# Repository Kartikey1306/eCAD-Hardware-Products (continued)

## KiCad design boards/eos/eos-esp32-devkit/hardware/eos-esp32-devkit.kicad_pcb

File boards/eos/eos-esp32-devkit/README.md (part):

# EoS ESP32 DevKit

A breadboard development board for the Espressif ESP32-WROOM-32E module, 27.94 × 48.76 mm, two layers.
Designed by Kartikeydheer Srivastava. All rights reserved: not open source, and not under this repository's MIT licence.
Anyone may view it, clone this repository and run its tests; anything more needs
Kartikeydheer Srivastava's written permission (kartikeydheer@gmail.com). EmbeddedOS (EoS) Research Foundation has a limited, revocable
permission. See [LICENSE.txt](LICENSE.txt) and [the licence summary](../README.md#licence).

A board for the same job as Espressif's ESP32-DevKitC V4; an original design, not a copy: no file of the vendor's was used.
The only things taken from Espressif's DevKitC V4 documents are facts it publishes for users: the header
pinout (the user guide's J2 and J3 tables) and the header grid and board width (its dimension drawing).
Its schematic, layout and board files were not opened.

| | |
|---|---|
|  |  |

USB-C in, a CP2102N USB-UART bridge with esptool's automatic reset into the bootloader, a 1 A
3.3 V regulator, EN and BOOT buttons, a power LED and a user LED, and every usable GPIO of the
module on two 1×19 headers.

## What is on it

| Block | What it is, and where each value comes from |
|---|---|
| Module | ESP32-WROOM-32E-N4 (4 MB flash, no PSRAM, so IO16 is free). 22 µF + 100 nF on 3V3 and the EN delay R = 10 kΩ, C = 1 µF: Espressif ESP32-WROOM-32E datasheet v2.1, section 9. The 100 nF and the 1 µF sit in the gap beside the module's 3V3 and EN pins. The module already has a 499 Ω resistor on U0TXD (datasheet Figure 7), as Espressif's hardware design guidelines ask, so none is added. |
| Antenna | The module's whole 6.19 mm antenna area (datasheet Figure 13) overhangs the top edge, 0.31 mm clear of it, so the antenna keep-out lies off the board. This is what the datasheet's section 11.2 refers to: Espressif's hardware design guidelines, "Positioning a Module on a Base Board", put the PCB antenna outside the base board. |
| 3.3 V supply | AP7361C-33 LDO, 1.0 A (Diodes Inc. DS37274 Rev. 5-2). The module needs at least 0.5 A at 3.0–3.6 V (datasheet Table 14) and draws 379 mA at its Wi-Fi TX peak, 239 mA on average (Table 16). Dropout is 140 mV at most at 300 mA. 4.7 µF on input and output, as the regulator's typical application shows. At a 253 mA average load from 4.1–4.8 V (USB's 4.75–5.25 V less the fuse and Schottky drops) it dissipates 0.20–0.39 W, 22–43 °C above ambient at the datasheet's 110 °C/W. |
| USB-C | 5 V sink: 5.1 kΩ Rd on CC1 and CC2 (TI SLVSFJ9, section 10.3.14.2), USB 2.0 data only. SP0503BAHTG ESD protection on D+, D− and VBUS: three diodes to ground, as the CP2102N data sheet shows (Figure 2.5). A USBLC6-style part, whose data-line diodes run to its VBUS pin, would let the CP2102N's D+ pull-up hold VBUS near 2 V after a host unplugs, when the board runs from its 5V pin. 500 mA polyfuse (Littelfuse 1206L050: 0.50 A hold, 1.00 A trip). Then a Nexperia PMEG6010CEH Schottky (60 V, 1 A; VF ≤ 530 mV at 500 mA) to the 5 V rail, so 5 V fed into the 5V pin cannot reach the USB host. It was chosen for its low reverse leakage. From a 4.75 V port at a 400 mA peak the regulator still gets at least 3.94 V. A 5.1 kΩ bleed resistor from VBUS to ground (R12) takes the Schottky's leakage when the board runs from the 5V pin with no host (see VBUS bleed below). |
| USB-UART | CP2102N-A02-GQFN24 (Silicon Labs data sheet Rev. 1.5). The QFN-24 has all eight UART and modem lines (DTR and RTS are the ones needed) in 4 × 4 mm. The QFN-28 is 5 × 5 mm, and its extra pins (battery-charger detection, GPIO.4–6) have no use here. It runs from the 3.3 V rail with its own regulator unused (Figure 2.3), so it is powered whenever the ESP32 is, and the ESP32's TX line never back-powers it. 4.7 µF + 100 nF on VREGIN/VDD and on VIO; 1 kΩ RSTb pull-up (section 2.1). VBUS sense through the 22.1 kΩ / 47.5 kΩ divider (Figures 2.5, 2.6), which section 2.3 requires: 5 V reads as 3.41 V, above the 2.7 V threshold. |
| Auto-program | The two-transistor circuit the esptool documentation describes ("Boot Mode Selection", "Automatic Bootloader"): RTS drives EN, DTR drives IO0, and asserting both together resets nothing. Two MMBT3904 (onsemi), each with its base through 10 kΩ from one line and its emitter on the other. The 10 kΩ gives at least 0.115 mA of base current (CP2102N Table 3.7 levels, MMBT3904 VBE(sat) ≤ 0.85 V) against a 0.33 mA load, so the transistor saturates. Discharging the EN capacitor it passes at most 78 mA into the CP2102N pin, under its 100 mA limit (Table 3.10). The 1 µF on EN is the "1 µF–10 µF" esptool asks for. |
| Buttons | EN (reset) and BOOT (IO0 to ground). IO0 has a 10 kΩ pull-up and no capacitor: Espressif's guidelines ("Strapping Pins") recommend a pull-up on GPIO0 and warn against large capacitors on it. |
| LEDs | Power (red, Kingbright APTD1608LSURCK, VF 1.75 V at 2 mA) through 750 Ω from 3.3 V. User LED (green, APTD1608LCGCK, VF 1.9 V at 2 mA) through 680 Ω on IO4, about 2 mA each. IO4 is not a strapping, JTAG, flash or UART0 pin, and its ADC2 channel cannot be used while Wi-Fi is on. It is pulled down at reset, so the LED starts off. |
| Headers | Two 1×19 rows, 2.54 mm pitch, 25.40 mm apart, on the grid of Espressif's ESP32-DevKitC V4 dimension drawing, in the order of its user guide's J2 and J3 tables. Pin labels are on the back. |

### VBUS bleed

When the board is fed from the 5V pin with no host plugged in, the Schottky is reverse-biased
by about 5 V and leaks into VBUS. Without R12, the CP2102N's 69.6 kΩ VBUS divider would be the
only load on that current, so VBUS could rise until the CP2102N saw a bus that is not there.

The CP2102N is guaranteed to read its VBUS pin as low at or below VIL = 0.6 V. It detects a
bus above VIH = VIO − 0.6 V = 2.7 V (data sheet Rev. 1.5, Table 3.7 and section 2.3). The
divider puts 47.5/69.6 of VBUS on the pin, so VBUS may rise to 0.88 V. R12 in parallel with the
divider is 4.75 kΩ, so up to 185 µA of leakage is harmless.

The PMEG6010CEH leaks 0.8 µA typically at 5 V and 25 °C (Nexperia data sheet v.4, Table 7). Its
maximum, 50 µA at 25 °C, is given at 60 V, and Fig. 2 shows the current falling with the
voltage, so at 5 V it is lower still. That is under a third of the bound. Fig. 2's typical
curves give about 65 µA at 5 V and 85 °C and about 600 µA at 125 °C, so a typical part reaches
185 µA only at roughly 100 °C. The data sheet gives no maximum above 25 °C. Scaling Fig. 2 by
the 25 °C maximum-to-typical ratio (50/11) suggests the bound holds to about 75 °C; that is an
estimate, not a data sheet figure.

With a host attached, R12 draws 1.0 mA (5 mW). It is the same 5.1 kΩ part as the CC resistors.
The PMEG6010CEH's forward drop is higher than a low-voltage Schottky's (460 mV typical, 530 mV
maximum at 500 mA), which the supply budget above allows for.

### Headers

Pin 1 is at the antenna end. Pin numbers and names follow the ESP32-DevKitC V4 user guide.

| Pin | J2 (left) | J3 (right) |
|---|---|---|
| 1 | 3V3 | GND |
| 2 | EN | IO23 |
| 3 | IO36 (SENSOR_VP, input only) | IO22 |
| 4 | IO39 (SENSOR_VN, input only) | TX (IO1, U0TXD) |
| 5 | IO34 (input only) | RX (IO3, U0RXD) |
| 6 | IO35 (input only) | IO21 |
| 7 | IO32 | GND |
| 8 | IO33 | IO19 |
| 9 | IO25 | IO18 |
| 10 | IO26 | IO5 (strapping) |
| 11 | IO27 | IO17 |
| 12 | IO14 | IO16 |
| 13 | IO12 (strapping: keep low at reset) | IO4 (user LED) |
| 14 | GND | IO0 (BOOT) |
| 15 | IO13 | IO2 (strapping: low or open to flash) |
| 16 | not connected | IO15 (strapping) |
| 17 | not connected | not connected |
| 18 | not connected | not connected |
| 19 | 5V | not connected |

The six unconnected positions are where the DevKitC V4 tables put D0–D3, CMD and CLK, which
are GPIO6–GPIO11. On the ESP32-WROOM-32E those lines run to the module's own SPI flash and are
not led out: the datasheet lists module pins 17–22 as NC (Table 3, note 2). They stay
unconnected here, so nothing can be wired to the flash bus.

Power: USB-C, the 5V pin and the 3V3 pin can each power the board. Espressif's DevKitC V4 guide
says to use one and only one supply on its board. This board allows one combination more:
USB-C and the 5V pin may be connected together. The Schottky between VBUS and the 5 V rail
stops the 5V-pin supply feeding back into the USB host. The board then runs from the 5V pin
unless that is lower than VBUS less the Schottky's drop. The 3V3 pin is wired straight to the
regulator's output, so use it as an input only when nothing is connected to USB-C or the 5V
pin.

The module overhangs the top edge by about 6.5 mm (its antenna end is 6.50 mm past the edge).
A panel of these boards needs a clear zone at least that deep above the top edge, with no
frame or neighbouring board in it.

The board is 0.50 mm longer than the DevKitC V4's 48.26 mm. The pin rows start 1.75 mm below
the top edge instead of 1.25 mm, because the header courtyards must clear the module
footprint's antenna keep-out courtyard. The grid itself (row spacing, pitch, side margins,
bottom margin) is unchanged, so the board fits the same breadboard rows and carrier sockets.

## Not on this board

- **Other modules.** Espressif sells the DevKitC V4 with several modules (WROOM-32UE, WROVER-E
  and others). This board is for the ESP32-WROOM-32E only, without PSRAM.
- **GPIO6–GPIO11 on the headers.** The WROOM-32E does not lead them out (see above).
- **Female headers.** The DevKitC V4 is also sold with female headers. This design uses male
  pin headers.
- **The DevKitC V4's exact length.** It is 0.50 mm longer, for the reason given above.
- **Mounting holes.** There is no room between the header rows for them. The board is meant
  for a breadboard or a socket.
- **An on-board debug probe.** The DevKitC V4 has none, and neither does this board. The
  module's JTAG pins (IO12 MTDI, IO13 MTCK, IO14 MTMS, IO15 MTDO) are on the headers for an
  external JTAG adapter.

## Build results

The numbers below are from `build-report.json` and `drc.json` in this folder.

| Check | Result |
|---|---|
| Schematic ERC | 0 violations |
| DRC errors | 0 |
| Unconnected items | 0 |
| Schematic ↔ board parity | 0 differences |
| DRC warnings | 8: silkscreen past the board edge: the header rows and the USB-C connector sit at the edge, and the module's outline runs over its antenna overhang |

## Fabrication

2 layers, 1.6 mm thick, ground poured on both sides. Design rules:

- **Tracks:** 0.15 mm, narrowing to the 0.1 mm minimum at fine-pitch pads; 0.4 mm on the
  supplies (VBUS, the fuse-to-Schottky link, 5 V and 3.3 V); 0.2 mm on USB D+/D−.
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
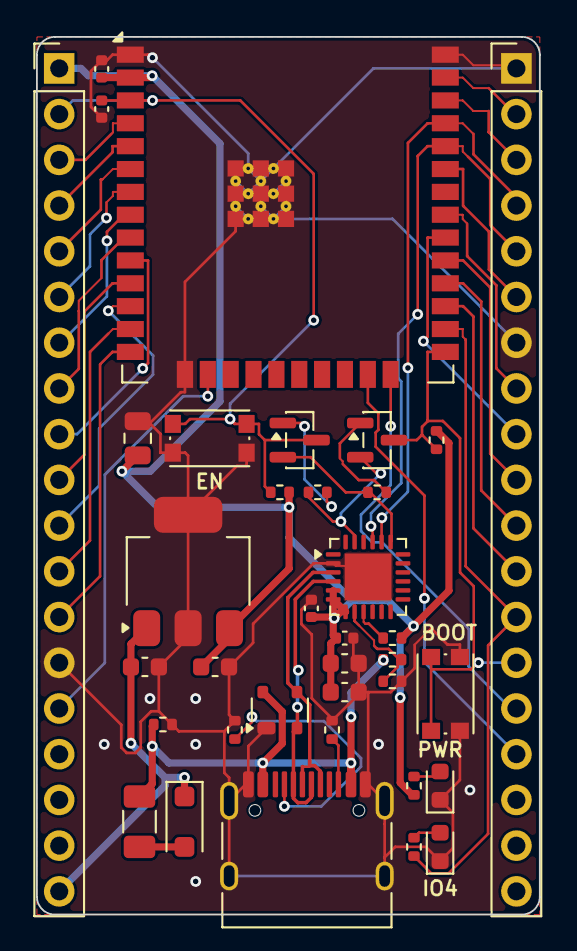
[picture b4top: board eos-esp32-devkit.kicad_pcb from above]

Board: 2 copper layers, 27.9 x 48.8 mm, 36 parts (0 on the bottom side), 44 nets.

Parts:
C1, C2, C6, C8: 4.7u; C_0603_1608Metric
C3, C7, C9: 100n; C_0402_1005Metric
C4: 22u; C_0805_2012Metric
C5: 1u; C_0402_1005Metric
D1: PMEG6010CEH; D_SOD-123F
D2: PWR; LED_0603_1608Metric
D3: IO4; LED_0603_1608Metric
F1: 500mA; Fuse_1206_3216Metric
J1: USB-C; USB_C_Receptacle_HRO_TYPE-C-31-M-12
J2: J2; PinHeader_1x19_P2.54mm_Vertical
J3: J3; PinHeader_1x19_P2.54mm_Vertical
Q1, Q2: MMBT3904; SOT-23
R1, R2, R12: 5.1k; R_0402_1005Metric
R3: 750; R_0402_1005Metric
R4, R5, R10, R11: 10k; R_0402_1005Metric
R6: 680; R_0402_1005Metric
R7: 1k; R_0402_1005Metric
R8: 22.1k; R_0402_1005Metric
R9: 47.5k; R_0402_1005Metric
SW1: EN; SW_Push_1P1T_NO_CK_KMR2
SW2: BOOT; SW_Push_1P1T_NO_CK_KMR2
U1: ESP32-WROOM-32E-N4; ESP32-WROOM-32E
U2: SP0503BAHTG; SOT-143
U3: AP7361C-33; SOT-223-3_TabPin2
U4: CP2102N-A02-GQFN24; QFN-24-1EP_4x4mm_P0.5mm_EP2.6x2.6mm

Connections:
+3V3: C2.1, C3.1, C4.1, C6.1, C7.1, C8.1, C9.1, J2.1, R3.1, R4.2, R5.2, R7.2, U1.2, U3.3, U4.5, U4.6, U4.7
+5V: C1.1, D1.1, J2.19, U3.1
/CC1: J1.A5, R1.1
/CC2: J1.B5, R2.1
/CP_RST: R7.1, U4.9
/DTR: Q2.2, R10.1, U4.23
/EN: C5.2, J2.2, Q1.3, R4.1, SW1.1, U1.3
/IO0: J3.14, Q2.3, R5.1, SW2.1, U1.25
/IO2: J3.15, U1.24
/IO4: J3.13, R6.1, U1.26
/IO5: J3.10, U1.29
/IO12: J2.13, U1.14
/IO13: J2.15, U1.16
/IO14: J2.12, U1.13
/IO15: J3.16, U1.23
/IO16: J3.12, U1.27
/IO17: J3.11, U1.28
/IO18: J3.9, U1.30
/IO19: J3.8, U1.31
/IO21: J3.6, U1.33
/IO22: J3.3, U1.36
/IO23: J3.2, U1.37
/IO25: J2.9, U1.10
/IO26: J2.10, U1.11
/IO27: J2.11, U1.12
/IO32: J2.7, U1.8
/IO33: J2.8, U1.9
/IO34: J2.5, U1.6
/IO35: J2.6, U1.7
/IO36: J2.3, U1.4
/IO39: J2.4, U1.5
/LED_PWR_A: D2.2, R3.2
/LED_USR_A: D3.2, R6.2
/QB1: Q1.1, R10.2
/QB2: Q2.1, R11.2
/RTS: Q1.2, R11.1, U4.19
/U0RXD: J3.5, U1.34, U4.21
/U0TXD: J3.4, U1.35, U4.20
/USB_D+: J1.A6, J1.B6, U2.3, U4.3
/USB_D-: J1.A7, J1.B7, U2.2, U4.4
/VBUS_F: D1.2, F1.2
/VBUS_SENSE: R8.2, R9.1, U4.8
GND: C1.2, C2.2, C3.2, C4.2, C5.1, C6.2, C7.2, C8.2, C9.2, D2.1, D3.1, J1.A1, J1.A12, J1.B1, J1.B12, J1.SH, J2.14, J3.1, J3.7, R1.2, R2.2, R9.2, R12.2, SW1.2, SW2.2, U1.1, U1.15, U1.38, U1.39, U2.1, U3.2, U4.2, U4.25
VBUS: F1.1, J1.A4, J1.A9, J1.B4, J1.B9, R8.1, R12.1, U2.4

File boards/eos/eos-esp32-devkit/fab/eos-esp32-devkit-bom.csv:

"Refs","Value","Footprint","Manufacturer","MPN","Description","Qty","DNP"
"C1,C2,C6,C8","4.7u","Capacitor_SMD:C_0603_1608Metric","","","Capacitor 4.7 uF 10 V X5R 0603 (CP2102N VIO, Silicon Labs CP2102N data sheet Rev. 1.5 section 2.1),Capacitor 4.7 uF 10 V X5R 0603 (CP2102N VREGIN/VDD, Silicon Labs CP2102N data sheet Rev. 1.5 Figure 2.3),Capacitor 4.7 uF 10 V X5R 0603 (LDO input; DS37274 typical application),Capacitor 4.7 uF 10 V X5R 0603 (LDO output; DS37274 typical application)","4",""
"C3,C7,C9","100n","Capacitor_SMD:C_0402_1005Metric","","","Capacitor 100 nF X7R 0402 (CP2102N VIO, Silicon Labs CP2102N data sheet Rev. 1.5 section 2.1),Capacitor 100 nF X7R 0402 (CP2102N VREGIN/VDD, Silicon Labs CP2102N data sheet Rev. 1.5 Figure 2.3),Capacitor 100 nF X7R 0402 (module 3V3, C2 in Espressif ESP32-WROOM-32E datasheet v2.1 section 9)","3",""
"C4","22u","Capacitor_SMD:C_0805_2012Metric","","","Capacitor 22 uF 10 V X5R 0805 (module 3V3, C1 in Espressif ESP32-WROOM-32E datasheet v2.1 section 9)","1",""
"C5","1u","Capacitor_SMD:C_0402_1005Metric","","","Capacitor 1 uF X7R 0402 (EN RC delay, Espressif ESP32-WROOM-32E datasheet v2.1 section 9; esptool needs 1-10 uF on EN for auto-reset)","1",""
"D1","PMEG6010CEH","Diode_SMD:D_SOD-123F","Nexperia","PMEG6010CEH","Schottky 60 V 1 A, VF <= 530 mV at 500 mA, IR 0.8 uA typ at 5 V, <= 50 uA at 25 C (Nexperia PMEG6010CEH v.4): the 5V pin cannot feed the USB host","1",""
"D2","PWR","LED_SMD:LED_0603_1608Metric","Kingbright","APTD1608LSURCK","LED red 0603, power (VF 1.75 V typ at 2 mA, DSAO7433)","1",""
"D3","IO4","LED_SMD:LED_0603_1608Metric","Kingbright","APTD1608LCGCK","LED green 0603, user LED on IO4 (VF 1.9 V typ at 2 mA, DSAO7432)","1",""
"F1","500mA","Fuse:Fuse_1206_3216Metric","Littelfuse","1206L050YR","PTC resettable fuse 0.50 A hold, 1.00 A trip, 6 V, 1206 (Littelfuse 1206L datasheet)","1",""
"J1","USB-C","Connector_USB:USB_C_Receptacle_HRO_TYPE-C-31-M-12","Korean Hroparts","TYPE-C-31-M-12","USB-C 2.0 receptacle, 16 pins (USB 2.0 only)","1",""
"J2","J2","Connector_PinHeader_2.54mm:PinHeader_1x19_P2.54mm_Vertical","","","Pin header 1x19 2.54 mm, left row (DevKitC V4 J2 pinout; 16-18 unconnected)","1",""
"J3","J3","Connector_PinHeader_2.54mm:PinHeader_1x19_P2.54mm_Vertical","","","Pin header 1x19 2.54 mm, right row (DevKitC V4 J3 pinout; 17-19 unconnected)","1",""
"Q1,Q2","MMBT3904","Package_TO_SOT_SMD:SOT-23","onsemi","MMBT3904LT1G","NPN, auto-boot: DTR low (RTS high) pulls IO0 low,NPN, auto-reset: RTS low (DTR high) pulls EN low","2",""
"R1,R2,R12","5.1k","Resistor_SMD:R_0402_1005Metric","","","Resistor 5.1 kohm 1% 0402 (USB-C sink Rd on CC1, 5.1 kohm per TI SLVSFJ9 section 10.3.14.2),Resistor 5.1 kohm 1% 0402 (USB-C sink Rd on CC2, 5.1 kohm per TI SLVSFJ9 section 10.3.14.2),Resistor 5.1 kohm 1% 0402 (VBUS bleed: with the divider, 4.75 kohm, so up to 185 uA of D1 leakage keeps the CP2102N VBUS pin under VIL 0.6 V, Silicon Labs CP2102N data sheet Rev. 1.5 Table 3.7; PMEG6010CEH leaks <= 50 uA at 25 C; 1.0 mA from a host)","3",""
"R3","750","Resistor_SMD:R_0402_1005Metric","","","Resistor 750 ohm 1% 0402 (power LED, 2.1 mA at VF 1.75 V; Kingbright DSAO7433)","1",""
"R4,R5,R10,R11","10k","Resistor_SMD:R_0402_1005Metric","","","Resistor 10 kohm 1% 0402 (EN RC delay, Espressif ESP32-WROOM-32E datasheet v2.1 section 9),Resistor 10 kohm 1% 0402 (IO0 pull-up, Espressif guidelines 'Strapping Pins'; internal pull-up 45 kohm),Resistor 10 kohm 1% 0402 (Q1 base; >= 0.115 mA, MMBT3904LT1/D and CP2102N Table 3.7),Resistor 10 kohm 1% 0402 (Q2 base; >= 0.115 mA, MMBT3904LT1/D and CP2102N Table 3.7)","4",""
"R6","680","Resistor_SMD:R_0402_1005Metric","","","Resistor 680 ohm 1% 0402 (user LED, 2.1 mA at VF 1.9 V; Kingbright DSAO7432)","1",""
"R7","1k","Resistor_SMD:R_0402_1005Metric","","","Resistor 1 kohm 1% 0402 (CP2102N RSTb pull-up, Silicon Labs CP2102N data sheet Rev. 1.5 section 2.1)","1",""
"R8","22.1k","Resistor_SMD:R_0402_1005Metric","","","Resistor 22.1 kohm 1% 0402 (CP2102N VBUS divider, Silicon Labs CP2102N data sheet Rev. 1.5 Figure 2.5)","1",""
"R9","47.5k","Resistor_SMD:R_0402_1005Metric","","","Resistor 47.5 kohm 1% 0402 (CP2102N VBUS divider, Silicon Labs CP2102N data sheet Rev. 1.5 Figure 2.5)","1",""
"SW1","EN","Button_Switch_SMD:SW_Push_1P1T_NO_CK_KMR2","C&K","KMR221G LFS","Tactile switch, EN (reset)","1",""
"SW2","BOOT","Button_Switch_SMD:SW_Push_1P1T_NO_CK_KMR2","C&K","KMR221G LFS","Tactile switch, BOOT (IO0 low: download mode)","1",""
"U1","ESP32-WROOM-32E-N4","RF_Module:ESP32-WROOM-32E","Espressif","ESP32-WROOM-32E-N4","ESP32 module, 4 MB flash, no PSRAM, PCB antenna (pins 17-22 and 32 NC, datasheet v2.1 Table 3)","1",""
"U2","USBLC6-2SC6","Package_TO_SOT_SMD:SOT-23-6","STMicroelectronics","USBLC6-2SC6","USB ESD protection, D+/D- and VBUS (ST DS4260 Rev. 7)","1",""
"U3","AP7361C-33","Package_TO_SOT_SMD:SOT-223-3_TabPin2","Diodes Incorporated","AP7361C-33E-13","LDO 3.3 V 1.0 A, SOT-223 (Diodes DS37274 Rev. 5-2); module needs >= 0.5 A","1",""
"U4","CP2102N-A02-GQFN24","Package_DFN_QFN:QFN-24-1EP_4x4mm_P0.5mm_EP2.6x2.6mm","Silicon Labs","CP2102N-A02-GQFN24R","USB-UART bridge, QFN-24, own regulator unused (Silicon Labs CP2102N data sheet Rev. 1.5 Figure 2.3)","1",""

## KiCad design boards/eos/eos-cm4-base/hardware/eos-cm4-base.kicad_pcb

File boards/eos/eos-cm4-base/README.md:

# EoS CM4 Base

A carrier board for the Raspberry Pi Compute Module 4, 90 × 80 mm, four layers. Designed by
Kartikeydheer Srivastava. All rights reserved: not open source, and not under this repository's MIT licence.
Anyone may view it, clone this repository and run its tests; anything more needs
Kartikeydheer Srivastava's written permission (kartikeydheer@gmail.com). EmbeddedOS (EoS) Research Foundation has a limited, revocable
permission. See [LICENSE.txt](LICENSE.txt) and [the licence summary](../README.md#licence).

A board for the same job as Raspberry Pi's CM4 IO Board; an original design, not a copy: no file
of the CM4 IO Board was used. It is EoS CM5 Base's layout, changed where the CM4 differs. The
connector and hole positions are facts taken from the CM5 footprint that Raspberry Pi publishes
for carrier designs (the CM5 IO Board datasheet says it may be used in your own designs). They
are cross-checked against the dimensions in the CM4 datasheet's Figure 4.

| | |
|---|---|
|  |  |

## The module fits, to the nanometre

The CM4 plugs in through two 100-pin Hirose DF40C-100DS-0.4V connectors, giving 1.5 mm
stacking (CM4 datasheet, section 3.1).

**Where the connectors and holes go.** Figure 4 of the CM4 datasheet and Figure 4 of the CM5
datasheet show the same module:
- the same 55 × 40 mm outline;
- M2.5 holes inset 3.5 mm;
- connectors 3 mm from the long edges;
- the same wireless cut-out.

The CM5 datasheet (section 1.2) also says CM5 fits existing CM4 carrier boards. So the connector
pads and holes sit where `tools/eos_boards/reference/cm5_carrier.json` puts them. That file holds
facts from the CM5 footprint that Raspberry Pi publishes for carriers. A test also places the
holes and connector centres from Figure 4's own dimensions and checks they land in the same
spots.

**Which net each pin carries** comes from the CM4 datasheet's pinout (section 4). It is recorded
in `tools/eos_boards/reference/cm4_pins.json` by `extract_cm4.py`, with the datasheet's SHA-256.

`tests/unit/test_eos_boards.py` checks, at KiCad's 1 nm resolution:
- all 200 pads and the four holes;
- every ground, 5 V, 3.3 V and GPIO pin's net;
- that HDMI, camera, display, PCIe, 1.8 V and reserved pins stay unconnected.

## What is on it

| Block | How |
|---|---|
| Power in | **USB-C, 5 V / 3 A.** VBUS feeds the module's six +5V pins (4.75–5.25 V). The CM4 draws about 1.4 A when running (datasheet section 5.3), plus the USB-A port (0.5 A), the 3.3 V loads and the fan, so use a 5 V / 3 A supply; a computer's USB port may not power the board. The CM4 does not negotiate USB-C power, so CC1 and CC2 each have 5.1 kΩ to ground (a USB-C sink). They also go to AnalogIP1 and AnalogIP0, which the datasheet says are "typically connected to CC pin of Type C power connector". The header's 5 V pins share this rail with no diode, so a HAT must not feed 5 V while the board is off. |
| USB 2.0 | **One port, two connectors.** The CM4 has one USB 2.0 port. A jumper (J9 5–6) chooses where it goes: open, a TI TS3USB30E switch routes it to the USB-C connector (device: rpiboot flashing, gadget mode); fitted, to the USB-A connector (host). TI's truth table: S low, D = D1; S high, D = D2. The same line is USB_OTG_ID: "Internally pulled up. When grounded the CM4 becomes a USB host but the correct OS driver also needs to be used" (pin 101). **The OS sets the role.** USB is off until `otg_mode=1` in `config.txt` enables it (section 2.4), and the ID pin is read only in OTG mode, so set the jumper to match. Fit it for host use. Leave it open for rpiboot, which always needs it open, and for gadget use (for example `dtoverlay=dwc2,dr_mode=peripheral`). **The USB-A port** sits on the top edge beside the module's USB pins, so the host path is short; the generator does not match lengths. Its 5 V comes through a TPS2051C (0.5 A, enable active high), whose enable a 2N7002 drives. It is on only in host mode and only while the CM4's 3.3 V is up: tied straight to USB_OTG_ID, an active-low switch would turn on whenever that rail is down. There are 0.1 µF and 10 µF at the input and 0.1 µF ceramic and 150 µF at the output, after TI's application circuit (USB asks 120 µF per port). Both connectors have USBLC6-2SC6 ESD protection. |
| Gigabit Ethernet | As EoS CM5 Base: a TRXCOM TRJG0926HENL MagJack, pairs 0–3 to TRD0–3, centre tap through 100 nF, activity and speed LEDs (Ethernet_nLED3, nLED2) through 470 Ω, and two flow-through TPD4EUSB30 for ESD. The CM4 uses the same pins. |
| microSD (CM4 Lite) | As EoS CM5 Base: direct to SD_CLK, SD_CMD and SD_DAT0–3. The card's 3.3 V comes through an RT9742GGJ5 switch enabled by SD_PWR_ON. |
| 40-pin GPIO | The standard Raspberry Pi header. GPIO_VREF is tied to CM4_3.3V, as the datasheet requires for 3.3 V GPIO. |
| Controls and LEDs | **Reset:** RUN_PG can be "driven low (via a 220Ω resistor) to reset the CM4 CPU", so a reset button goes through 220 Ω. **Power LED:** PI_LED_nPWR "needs to be buffered", so a BSS84 P-MOSFET drives it. **Activity LED:** Pi_nLED_Activity sinks its LED directly (20 mA max). **Jumpers:** nRPIBOOT (USB boot), EEPROM write protect, USB host mode. **Fan:** a plain 5 V fan connector. |
| Antenna | **No copper on any layer under the module's PCB antenna.** The CM4 datasheet (section 3.1) says there must be no metal there, ground planes included, and a ground-plane cut-out of at least 6.5 × 11 mm, ideally 8 × 15 mm. The board keeps the larger area clear on every layer, where Figure 4 puts the antenna. A test checks it. |

## Not on this board

HDMI, PCIe, and the camera and display (MIPI CSI and DSI) interfaces are left off on purpose.
Each needs impedance-controlled, length-matched differential pairs. This generator routes nets
one at a time and cannot match or verify such pairs.

The CM4 has no RTC battery input and no fan-controller pins, so this board has no coin cell and
no fan speed control. Raspberry Pi's CM4 IO Board adds those with chips on I2C; this board does
not.

## Build results

The numbers below are from `build-report.json` and `drc.json` in this folder.

| Check | Result |
|---|---|
| Schematic ERC | 0 violations |
| DRC errors | 0 |
| Unconnected items | 0 |
| Schematic ↔ board parity | 0 differences |
| DRC warnings | 4: silkscreen of the USB-C connector (J3) and the RJ45 MagJack (J5) past the board edge, where edge connectors belong |

## Fabrication

4 layers (signal / GND plane / 5 V plane / signal), 1.6 mm thick.

- **Vias:** 0.45 mm with a 0.2 mm drill, as on EoS CM5 Base.
- **Tracks:** 0.15 mm by default and 0.2 mm on the USB and Ethernet lines, narrowing to the 0.09 mm
  four-layer minimum where the router enters a fine-pitch pad; 0.5 mm on 5 V where it is routed
  rather than on the plane.
- **Under the module:** nothing on the top side, because 1.5 mm stacking leaves no room. There is
  no copper at all under the antenna.

Some lines are routed first, in a set order, before the autorouter:
- the Ethernet pairs;
- the USB pair from the module to the switch;
- the host pair through its ESD part to the USB-A port;
- three microSD lines (DAT1, DAT0, CLK).

The power switch and the 150 µF capacitor sit more than 10 mm from the module's antenna.

## What has not been done

- **No board has been made or tested.**
- **No signal-integrity simulation.** The CM4 datasheet asks for 90 Ω differential pairs with P
  and N matched to 0.15 mm, and TI asks for equal-length USB lines. This generator routes each
  line on its own and matches no lengths, so the pairs are short but not matched, and their
  impedance has not been calculated or simulated.
- **The switch's effect on the USB eye** has not been measured. TI publishes a 480 Mb/s eye
  diagram through the TS3USB30E.

## Rebuild

```
python3 tools/eos_boards/build.py eos_cm4_base
```

The design file is [tools/eos_boards/boards/eos_cm4_base.py](../../../tools/eos_boards/boards/eos_cm4_base.py).

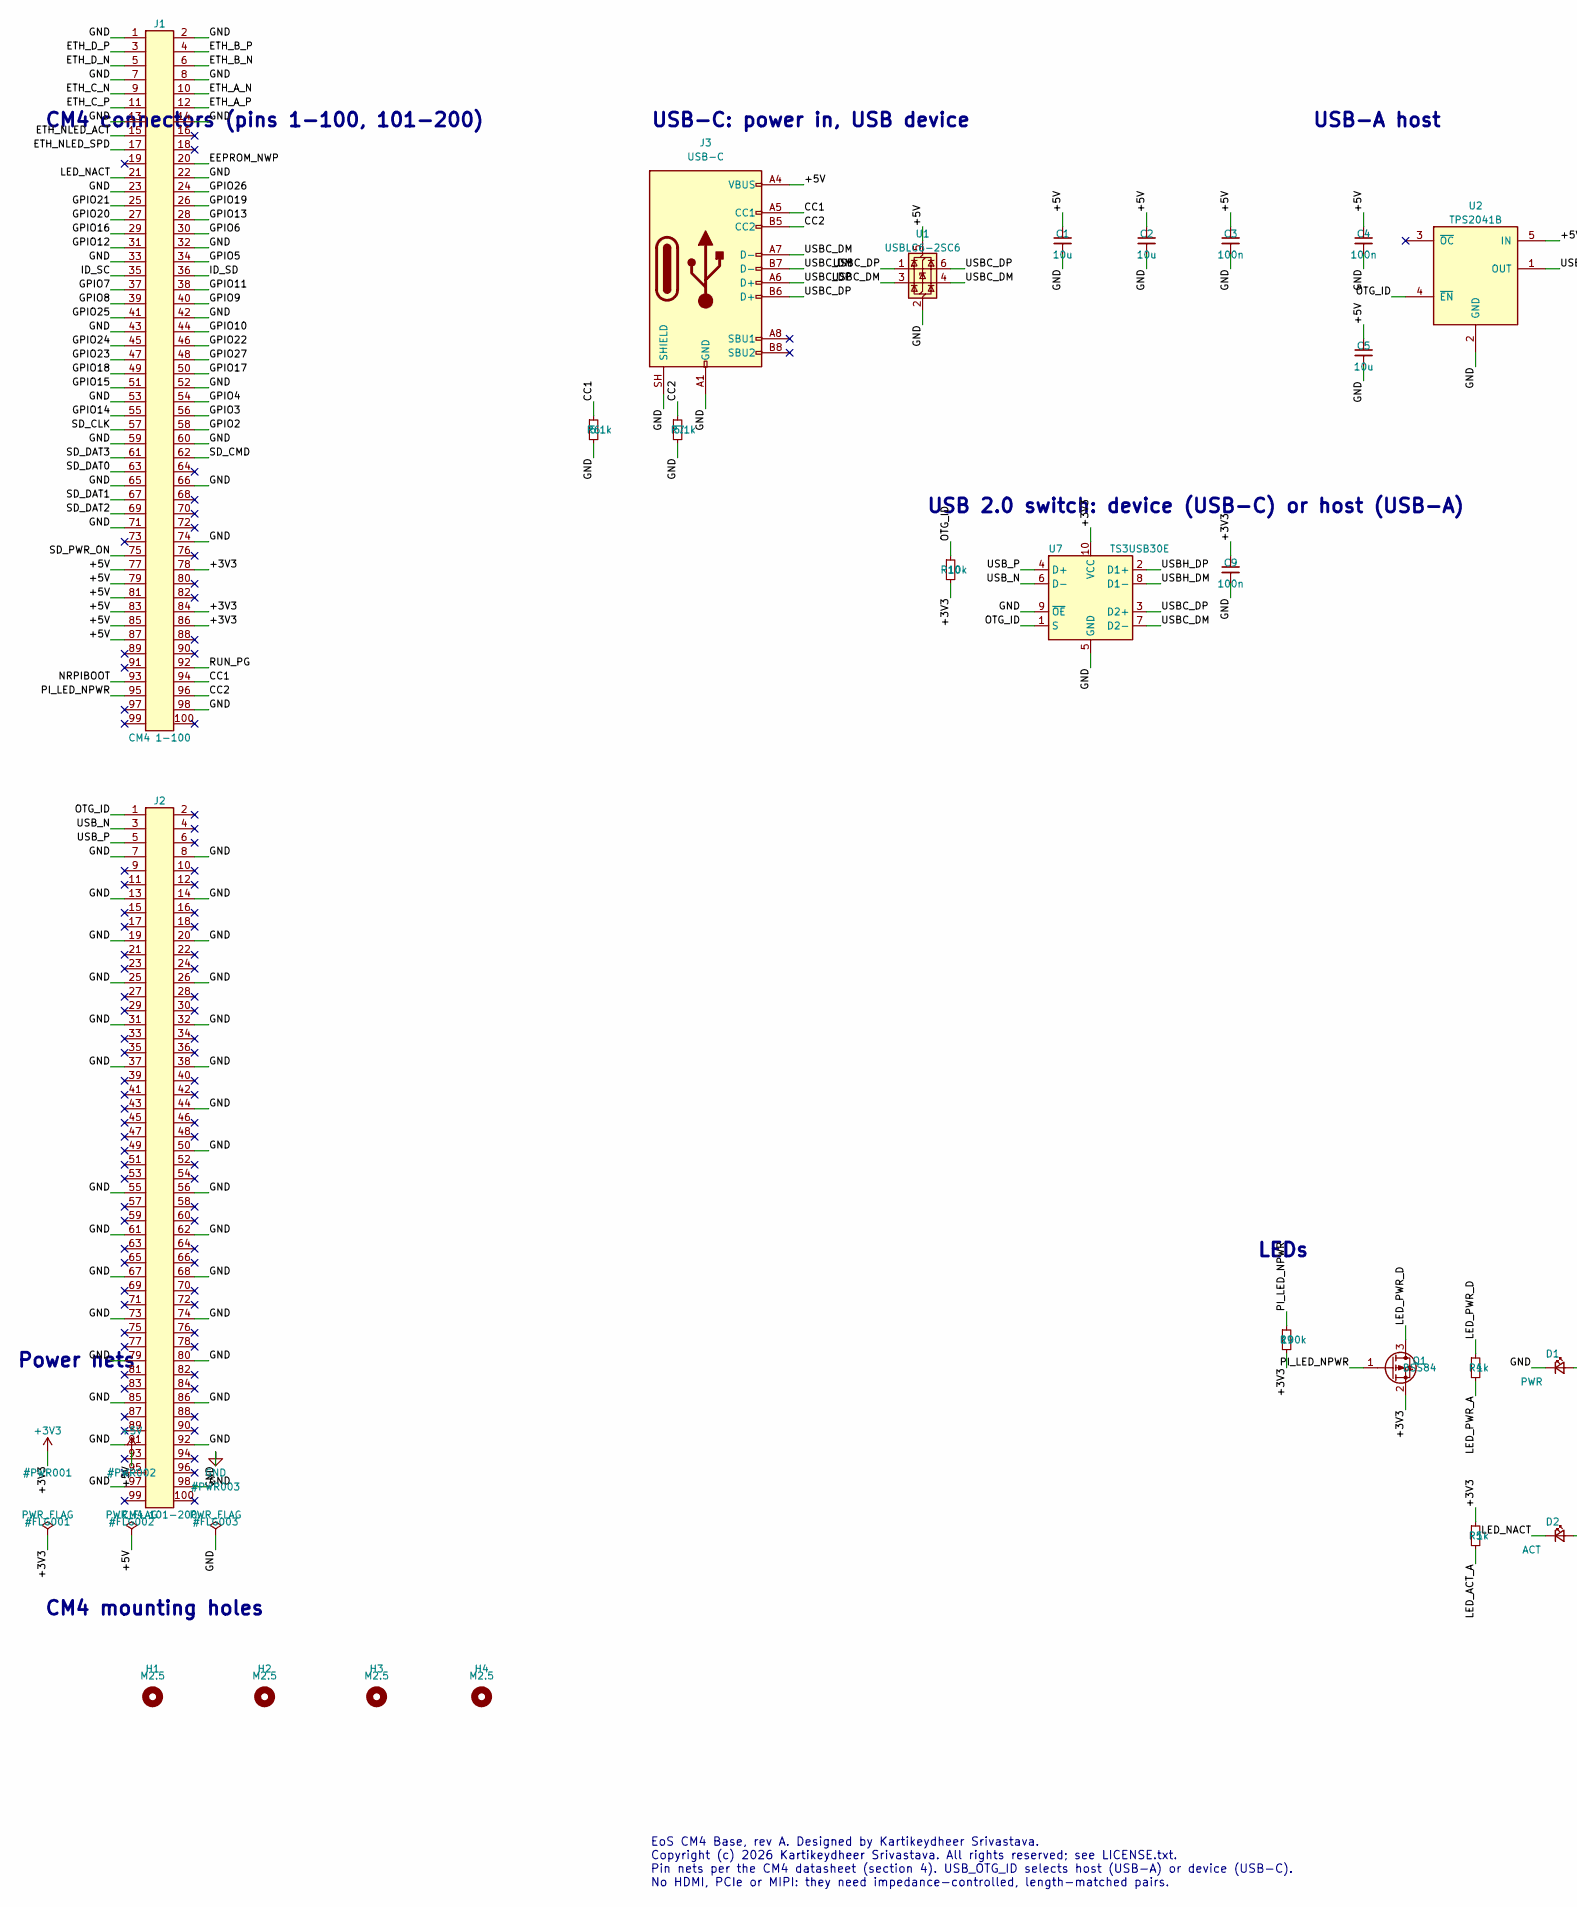
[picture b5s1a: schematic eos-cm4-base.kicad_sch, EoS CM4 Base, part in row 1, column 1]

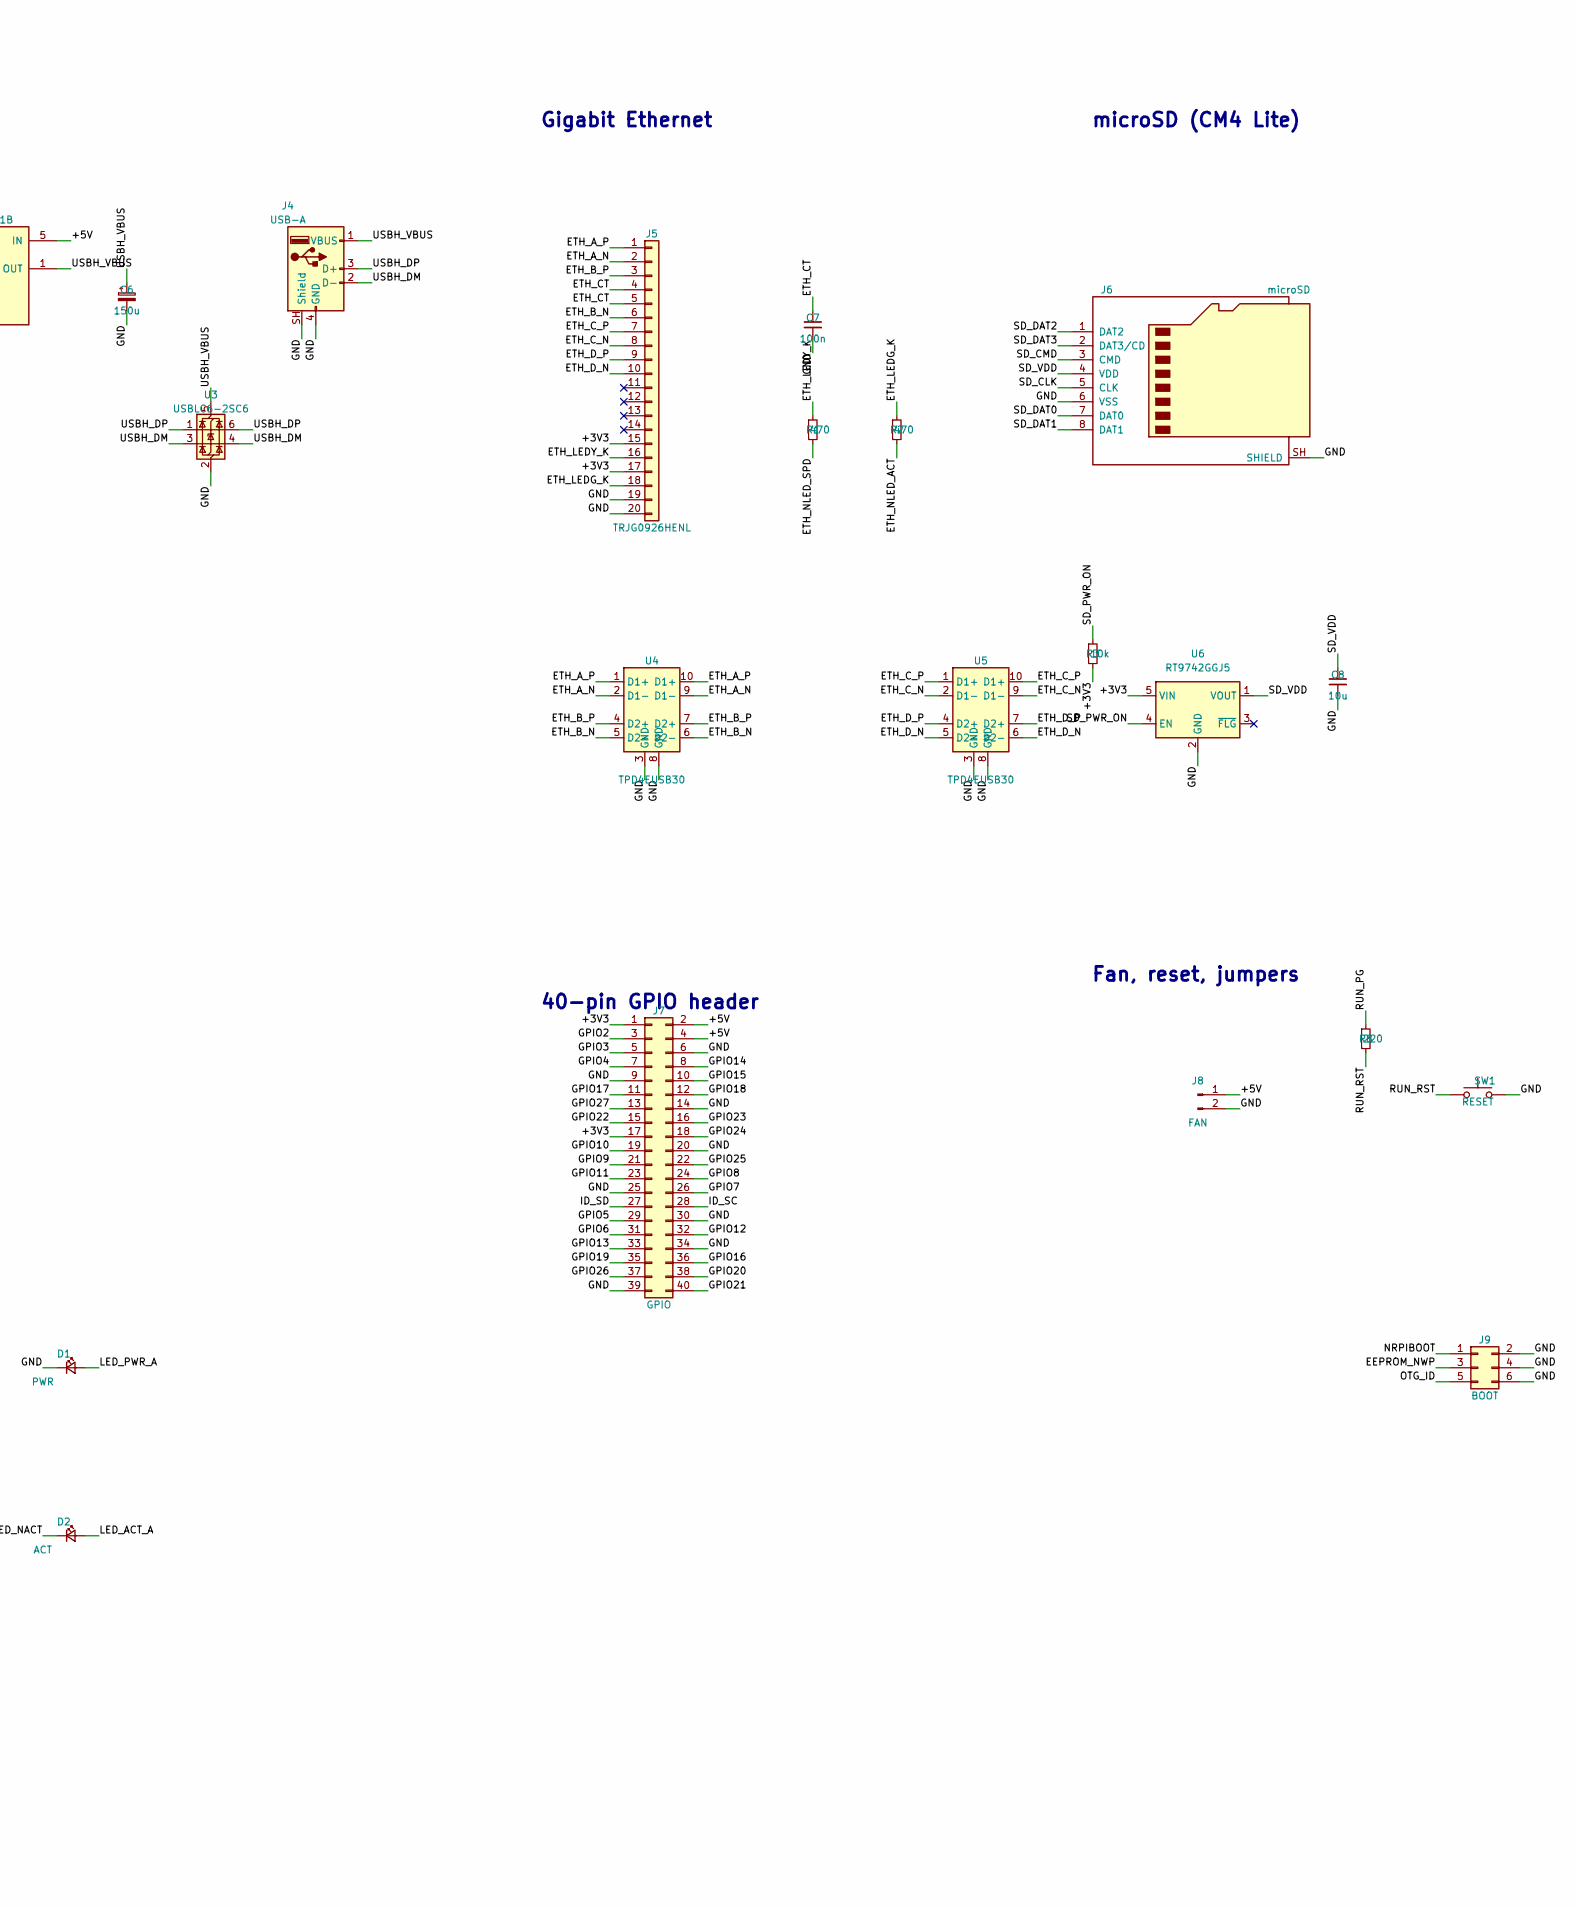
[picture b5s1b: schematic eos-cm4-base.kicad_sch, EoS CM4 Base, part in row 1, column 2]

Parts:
C1, C2, C5, C8: 10u; C_0805_2012Metric
C3, C4, C7, C9: 100n; C_0402_1005Metric
C6: 150u; CP_Elec_6.3x5.8; MPN EEE-FK1A151P
D1: PWR; LED_0603_1608Metric; MPN APTD1608LSURCK
D2: ACT; LED_0603_1608Metric; MPN APTD1608LCGCK
H1, H2, H3, H4: M2.5; MountingHole_2.7mm_M2.5
J1: CM4 1-100; Hirose_DF40C-100DS-0.4V_2x50_P0.4mm; MPN DF40C-100DS-0.4V(51)
J2: CM4 101-200; Hirose_DF40C-100DS-0.4V_2x50_P0.4mm; MPN DF40C-100DS-0.4V(51)
J3: USB-C; USB_C_Receptacle_HRO_TYPE-C-31-M-12; MPN TYPE-C-31-M-12
J4: USB-A; USB_A_Molex_67643_Horizontal; MPN 67643-0910
J5: TRJG0926HENL; TRXCOM_TRJG0926HENL; MPN TRJG0926HENL
J6: microSD; microSD_HC_Molex_104031-0811; MPN 104031-0811
J7: GPIO; PinHeader_2x20_P2.54mm_Vertical
J8: FAN; JST_SH_BM02B-SRSS-TB_1x02-1MP_P1.00mm_Vertical; MPN BM02B-SRSS-TB
J9: BOOT; PinHeader_2x03_P2.54mm_Vertical
Q1: BSS84; SOT-23; MPN BSS84,215
R1, R2: 470; R_0402_1005Metric
R3, R10: 10k; R_0402_1005Metric
R4, R5: 1k; R_0402_1005Metric
R6, R7: 5.1k; R_0402_1005Metric
R8: 220; R_0402_1005Metric
R9: 100k; R_0402_1005Metric
SW1: RESET; SW_Push_1P1T_NO_CK_KMR2; MPN KMR221G LFS
U1, U3: USBLC6-2SC6; SOT-23-6; MPN USBLC6-2SC6
U2: TPS2041B; SOT-23-5; MPN TPS2041BDBVR
U4, U5: TPD4EUSB30; USON-10_2.5x1.0mm_P0.5mm; MPN TPD4EUSB30DQAR
U6: RT9742GGJ5; TSOT-23-5; MPN RT9742GGJ5
U7: TS3USB30E; TSSOP-10_3x3mm_P0.5mm; MPN TS3USB30EDGSR

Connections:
+3V3: C9.1, J1.78, J1.84, J1.86, J5.15, J5.17, J7.1, J7.17, Q1.2 (S), R3.2, R5.1, R9.2, R10.2, U6.5 (VIN), U7.10 (VCC)
+5V: C1.1, C2.1, C3.1, C4.1, C5.1, J1.77, J1.79, J1.81, J1.83, J1.85, J1.87, J3.A4 (VBUS), J3.A9 (VBUS), J3.B4 (VBUS), J3.B9 (VBUS), J7.2, J7.4, J8.1, U1.5 (VBUS), U2.5 (IN)
/CC1: J1.94, J3.A5 (CC1), R6.1
/CC2: J1.96, J3.B5 (CC2), R7.1
/EEPROM_NWP: J1.20, J9.3
/ETH_A_N: J1.10, J5.2, U4.2 (D1-), U4.9 (D1-)
/ETH_A_P: J1.12, J5.1, U4.1 (D1+), U4.10 (D1+)
/ETH_B_N: J1.6, J5.6, U4.5 (D2-), U4.6 (D2-)
/ETH_B_P: J1.4, J5.3, U4.4 (D2+), U4.7 (D2+)
/ETH_CT: C7.1, J5.4, J5.5
/ETH_C_N: J1.9, J5.8, U5.2 (D1-), U5.9 (D1-)
/ETH_C_P: J1.11, J5.7, U5.1 (D1+), U5.10 (D1+)
/ETH_D_N: J1.5, J5.10, U5.5 (D2-), U5.6 (D2-)
/ETH_D_P: J1.3, J5.9, U5.4 (D2+), U5.7 (D2+)
/ETH_LEDG_K: J5.18, R2.1
/ETH_LEDY_K: J5.16, R1.1
/ETH_NLED_ACT: J1.15, R2.2
/ETH_NLED_SPD: J1.17, R1.2
/GPIO2: J1.58, J7.3
/GPIO3: J1.56, J7.5
/GPIO4: J1.54, J7.7
/GPIO5: J1.34, J7.29
/GPIO6: J1.30, J7.31
/GPIO7: J1.37, J7.26
/GPIO8: J1.39, J7.24
/GPIO9: J1.40, J7.21
/GPIO10: J1.44, J7.19
/GPIO11: J1.38, J7.23
/GPIO12: J1.31, J7.32
/GPIO13: J1.28, J7.33
/GPIO14: J1.55, J7.8
/GPIO15: J1.51, J7.10
/GPIO16: J1.29, J7.36
/GPIO17: J1.50, J7.11
/GPIO18: J1.49, J7.12
/GPIO19: J1.26, J7.35
/GPIO20: J1.27, J7.38
/GPIO21: J1.25, J7.40
/GPIO22: J1.46, J7.15
/GPIO23: J1.47, J7.16
/GPIO24: J1.45, J7.18
/GPIO25: J1.41, J7.22
/GPIO26: J1.24, J7.37
/GPIO27: J1.48, J7.13
/ID_SC: J1.35, J7.28
/ID_SD: J1.36, J7.27
/LED_ACT_A: D2.2 (A), R5.2
/LED_NACT: D2.1 (K), J1.21
/LED_PWR_A: D1.2 (A), R4.2
/LED_PWR_D: Q1.3 (D), R4.1
/NRPIBOOT: J1.93, J9.1
/OTG_ID: J2.1, J9.5, R10.1, U2.4 (~EN), U7.1 (S)
/PI_LED_NPWR: J1.95, Q1.1 (G), R9.1
/RUN_PG: J1.92, R8.1
/RUN_RST: R8.2, SW1.1
/SD_CLK: J1.57, J6.5 (CLK)
/SD_CMD: J1.62, J6.3 (CMD)
/SD_DAT0: J1.63, J6.7 (DAT0)
/SD_DAT1: J1.67, J6.8 (DAT1)
/SD_DAT2: J1.69, J6.1 (DAT2)
/SD_DAT3: J1.61, J6.2 (DAT3/CD)
/SD_PWR_ON: J1.75, R3.1, U6.4 (EN)
/SD_VDD: C8.1, J6.4 (VDD), U6.1 (VOUT)
/USBC_DM: J3.A7 (D-), J3.B7 (D-), U1.3 (I/O2), U1.4 (I/O2), U7.7 (D2-)
/USBC_DP: J3.A6 (D+), J3.B6 (D+), U1.1 (I/O1), U1.6 (I/O1), U7.3 (D2+)
/USBH_DM: J4.2 (D-), U3.3 (I/O2), U3.4 (I/O2), U7.8 (D1-)
/USBH_DP: J4.3 (D+), U3.1 (I/O1), U3.6 (I/O1), U7.2 (D1+)
/USBH_VBUS: C6.1, J4.1 (VBUS), U2.1 (OUT), U3.5 (VBUS)
/USB_N: J2.3, U7.6 (D-)
/USB_P: J2.5, U7.4 (D+)
GND: C1.2, C2.2, C3.2, C4.2, C5.2, C6.2, C7.2, C8.2, C9.2, D1.1 (K), J1.1, J1.2, J1.7, J1.8, J1.13, J1.14, J1.22, J1.23, J1.32, J1.33, J1.42, J1.43, J1.52, J1.53, J1.59, J1.60, J1.65, J1.66, J1.71, J1.74, J1.98, J2.7, J2.8, J2.13, J2.14, J2.19, J2.20, J2.25, J2.26, J2.31, J2.32, J2.37, J2.38, J2.44, J2.50, J2.55, J2.56, J2.61, J2.62, J2.67, J2.68, J2.73, J2.74, J2.79, J2.80, J2.85, J2.86, J2.91, J2.92, J2.97, J2.98, J3.A1 (GND), J3.A12 (GND), J3.B1 (GND), J3.B12 (GND), J3.SH (SHIELD), J4.4 (GND), J4.SH (Shield), J5.19, J5.20, J6.6 (VSS), J6.SH (SHIELD), J7.6, J7.9, J7.14, J7.20, J7.25, J7.30, J7.34, J7.39, J8.2, J9.2, J9.4, J9.6, R6.2, R7.2, SW1.2, U1.2 (GND), U2.2 (GND), U3.2 (GND), U4.3 (GND), U4.8 (GND), U5.3 (GND), U5.8 (GND), U6.2 (GND), U7.5 (GND), U7.9 (~OE)

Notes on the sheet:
CM4 connectors (pins 1-100, 101-200)
USB-C: power in, USB device
USB 2.0 switch: device (USB-C) or host (USB-A)
USB-A host
Gigabit Ethernet
microSD (CM4 Lite)
40-pin GPIO header
Fan, reset, jumpers
LEDs
CM4 mounting holes
Power nets
EoS CM4 Base, rev A. Designed by Kartikeydheer Srivastava. Copyright (c) 2026 Kartikeydheer Srivastava. All rights reserved; see LICENSE.txt. Pin nets per the CM4 datasheet (section 4). USB_OTG_ID selects host (USB-A) or device (USB-C). No HDMI, PCIe or MIPI: they need impedance-controlled, length-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

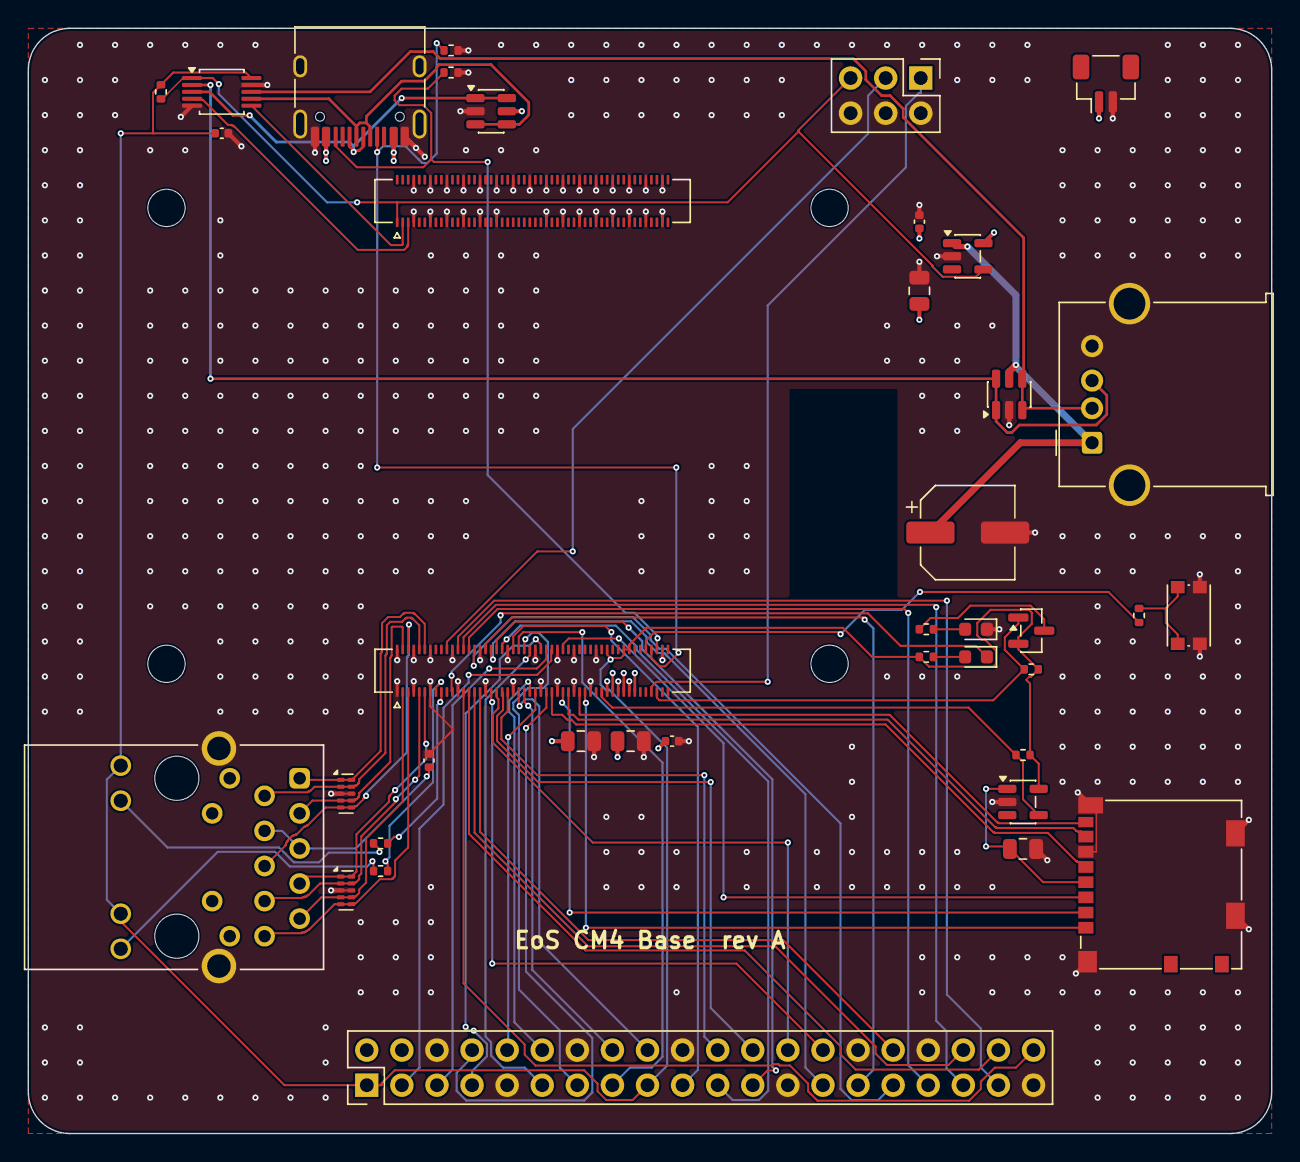
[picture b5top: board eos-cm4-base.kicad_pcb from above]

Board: 4 copper layers, 90.0 x 80.0 mm, 43 parts (0 on the bottom side), 71 nets.

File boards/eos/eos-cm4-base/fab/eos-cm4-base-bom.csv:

"Refs","Value","Footprint","Manufacturer","MPN","Description","Qty","DNP"
"C1,C2,C5,C8","10u","Capacitor_SMD:C_0805_2012Metric","","","Capacitor 10 uF 10 V X5R 0805 (5 V at the module),Capacitor 10 uF 10 V X5R 0805 (TPS2041B input bulk),Capacitor 10 uF 10 V X5R 0805 (microSD supply)","4",""
"C3,C4,C7,C9","100n","Capacitor_SMD:C_0402_1005Metric","","","Capacitor 100 nF X7R 0402 (5 V at the module),Capacitor 100 nF X7R 0402 (MagJack centre tap),Capacitor 100 nF X7R 0402 (TPS2041B input, 0.01-0.1 uF per TI),Capacitor 100 nF X7R 0402 (TS3USB30E VCC bypass, TI 8.3)","4",""
"C6","150u","Capacitor_SMD:CP_Elec_6.3x5.8","Panasonic","EEE-FK1A151P","Capacitor 150 uF 10 V aluminium, 6.3 x 5.8 mm (USB host port: 120 uF per TI)","1",""
"D1","PWR","LED_SMD:LED_0603_1608Metric","Kingbright","APTD1608LSURCK","LED red 0603, power (PI_LED_nPWR)","1",""
"D2","ACT","LED_SMD:LED_0603_1608Metric","Kingbright","APTD1608LCGCK","LED green 570 nm 0603, activity (Pi_nLED_Activity)","1",""
"J1","CM4 1-100","Connector_Hirose_DF40:Hirose_DF40C-100DS-0.4V_2x50_P0.4mm","Hirose","DF40C-100DS-0.4V(51)","CM4 connector, pins 1-100, 1.5 mm stacking (CM4 datasheet 3.1)","1",""
"J2","CM4 101-200","Connector_Hirose_DF40:Hirose_DF40C-100DS-0.4V_2x50_P0.4mm","Hirose","DF40C-100DS-0.4V(51)","CM4 connector, pins 101-200, 1.5 mm stacking (CM4 datasheet 3.1)","1",""
"J3","USB-C","Connector_USB:USB_C_Receptacle_HRO_TYPE-C-31-M-12","Korean Hroparts","TYPE-C-31-M-12","USB-C 2.0 receptacle (power in, USB device)","1",""
"J4","USB-A","Connector_USB:USB_A_Molex_67643_Horizontal","Molex","67643-0910","USB-A receptacle, USB 2.0 host","1",""
"J5","TRJG0926HENL","EoS_Connectors:TRXCOM_TRJG0926HENL","TRXCOM","TRJG0926HENL","RJ45 MagJack 10/100/1000, LEDs","1",""
"J6","microSD","Connector_Card:microSD_HC_Molex_104031-0811","Molex","104031-0811","microSD socket (CM4 Lite)","1",""
"J7","GPIO","Connector_PinHeader_2.54mm:PinHeader_2x20_P2.54mm_Vertical","","","Raspberry Pi 40-pin GPIO header","1",""
"J8","FAN","Connector_JST:JST_SH_BM02B-SRSS-TB_1x02-1MP_P1.00mm_Vertical","JST","BM02B-SRSS-TB","Fan: 1 5 V, 2 GND (the CM4 has no fan pins)","1",""
"J9","BOOT","Connector_PinHeader_2.54mm:PinHeader_2x03_P2.54mm_Vertical","","","Jumpers: 1-2 nRPIBOOT (USB boot), 3-4 EEPROM write protect, 5-6 USB host mode","1",""
"Q1","BSS84","Package_TO_SOT_SMD:SOT-23","Nexperia","BSS84,215","P-MOSFET, power LED buffer (PI_LED_nPWR needs buffering)","1",""
"R1,R2","470","Resistor_SMD:R_0402_1005Metric","","","Resistor 470 ohm 1% 0402 (green LED, activity),Resistor 470 ohm 1% 0402 (yellow LED, speed)","2",""
"R3,R10","10k","Resistor_SMD:R_0402_1005Metric","","","Resistor 10 kohm 1% 0402 (SD_PWR_ON pull-up),Resistor 10 kohm 1% 0402 (USB_OTG_ID high: device mode by default)","2",""
"R4,R5","1k","Resistor_SMD:R_0402_1005Metric","","","Resistor 1 kohm 1% 0402 (activity LED),Resistor 1 kohm 1% 0402 (power LED)","2",""
"R6,R7","5.1k","Resistor_SMD:R_0402_1005Metric","","","Resistor 5.1 kohm 1% 0402 (USB-C sink, CC1; also to AnalogIP1),Resistor 5.1 kohm 1% 0402 (USB-C sink, CC2; also to AnalogIP0)","2",""
"R8","220","Resistor_SMD:R_0402_1005Metric","","","Resistor 220 ohm 1% 0402 (RUN_PG reset, CM4 datasheet pin 92)","1",""
"R9","100k","Resistor_SMD:R_0402_1005Metric","","","Resistor 100 kohm 1% 0402 (keeps the LED buffer off while PI_LED_nPWR floats)","1",""
"SW1","RESET","Button_Switch_SMD:SW_Push_1P1T_NO_CK_KMR2","C&K","KMR221G LFS","Reset button (RUN_PG through 220 ohm)","1",""
"U1,U3","USBLC6-2SC6","Package_TO_SOT_SMD:SOT-23-6","STMicroelectronics","USBLC6-2SC6","USB ESD protection (USB-C),USB ESD protection (host port)","2",""
"U2","TPS2041B","Package_TO_SOT_SMD:SOT-23-5","Texas Instruments","TPS2041BDBVR","USB power switch 0.5 A, enable active low: on in host mode","1",""
"U4,U5","TPD4EUSB30","Package_SON:USON-10_2.5x1.0mm_P0.5mm","Texas Instruments","TPD4EUSB30DQAR","ESD protection, Ethernet pairs A and B, flow-through as TI lays it out,ESD protection, Ethernet pairs C and D, flow-through as TI lays it out","2",""
"U6","RT9742GGJ5","Package_TO_SOT_SMD:TSOT-23-5","Richtek","RT9742GGJ5","Load switch for the microSD supply, enable high","1",""
"U7","TS3USB30E","Package_SO:TSSOP-10_3x3mm_P0.5mm","Texas Instruments","TS3USB30EDGSR","USB 2.0 2:1 switch: S low (host) to USB-A, S high (device) to USB-C","1",""
